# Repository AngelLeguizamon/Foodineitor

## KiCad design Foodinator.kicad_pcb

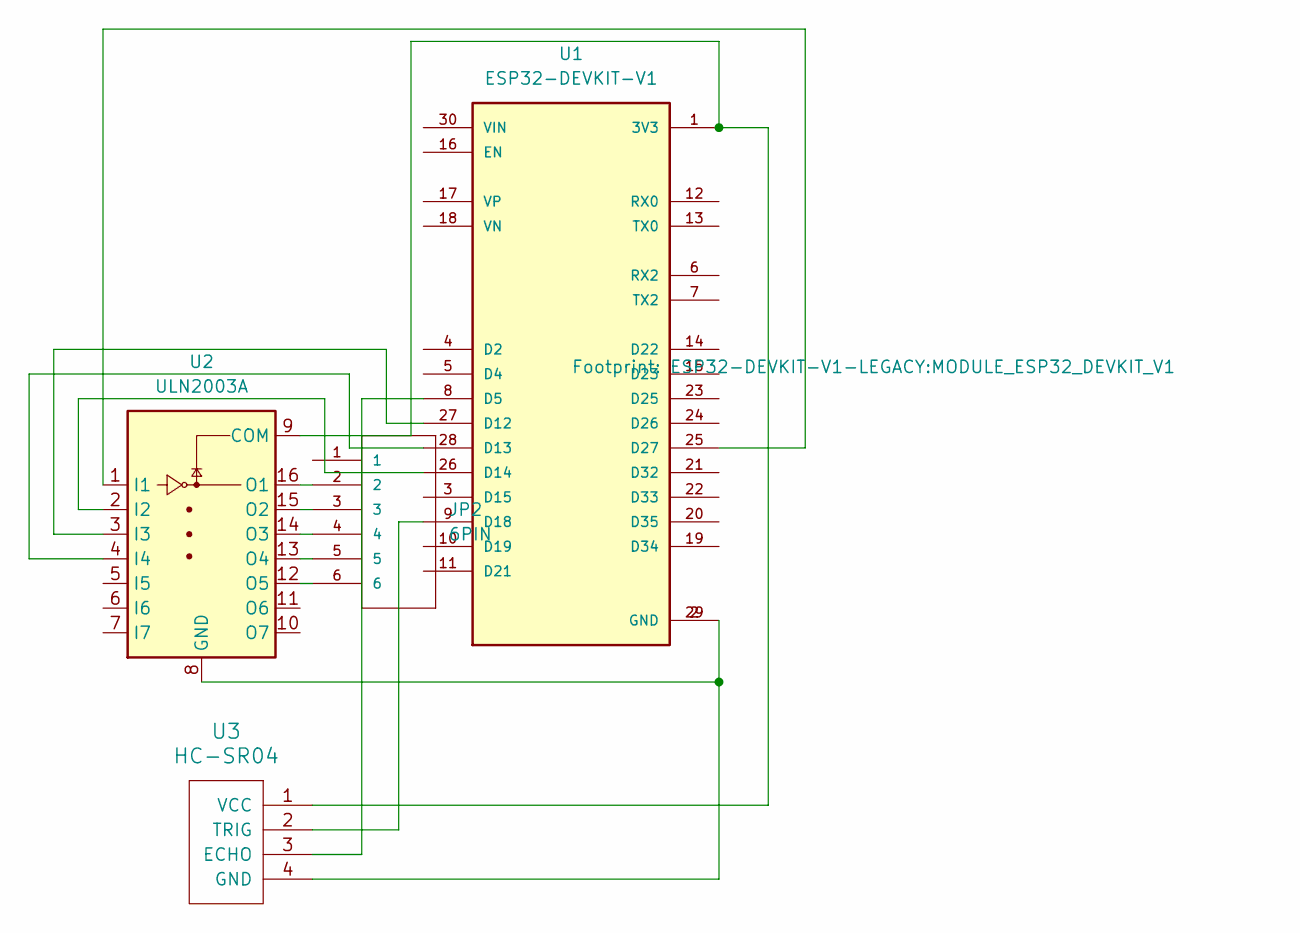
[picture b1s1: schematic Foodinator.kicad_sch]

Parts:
JP2: 6PIN; jst_eph-B6B-PH-K-S
U1: ESP32-DEVKIT-V1; MODULE_ESP32_DEVKIT_V1; PARTREV N/A
U2: ULN2003A; DIP794W45P254L1969H508Q16
U3: HC-SR04; XCVR_HC-SR04

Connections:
unnamed: U1.1 (3V3), U2.9 (COM), U3.1 (VCC)
unnamed: U1.8 (D5), U3.3 (ECHO)
unnamed: U1.27 (D12), U2.3 (I3)
unnamed: U1.28 (D13), U2.4 (I4)
unnamed: U1.26 (D14), U2.2 (I2)
unnamed: U1.9 (D18), U3.2 (TRIG)
unnamed: U1.25 (D27), U2.1 (I1)
unnamed: U1.2 (GND), U1.29 (GND), U2.8 (GND), U3.4 (GND)
unnamed: JP2.2, U2.16 (O1)
unnamed: JP2.3, U2.15 (O2)
unnamed: JP2.4, U2.14 (O3)
unnamed: JP2.5, U2.13 (O4)
unnamed: JP2.6, U2.12 (O5)

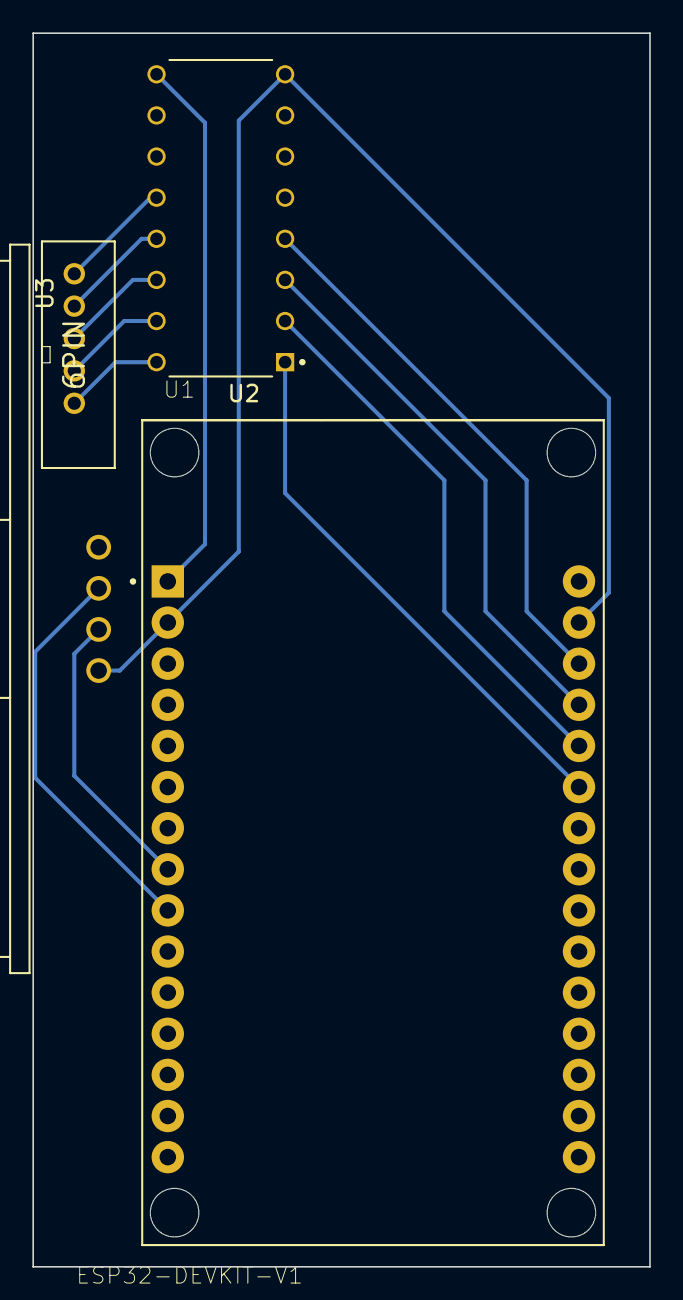
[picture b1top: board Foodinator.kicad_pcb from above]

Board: 2 copper layers, 38.1 x 76.2 mm, 4 parts (0 on the bottom side), 13 nets.

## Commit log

2023-12-01 Create Esquema mal
